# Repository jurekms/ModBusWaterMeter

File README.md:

# ModBusWaterMeter
Nakładka na wodomierz zliczająca impulsy ,udostępniająca dane za pomocą protokołu MODBUS poprzez interfejs RS485.
Nakładka na wodomierz zliczająca ilość obrotów dwubarwnej tarczy znajdującej się na panelu odczytowym wodomierza. Optyczny układ przystawki oświetla tarczę obrotową wodomierza światłem IR, które jest odbijane (część lustrzana tarczy) lub pochłaniane (część czarna tarczy), odbita wiązka jest rejestrowana przez fototranzystor z którego sygnał analogowy kierowany jest do komparatora okienkowego zbudowanego na układzie LM393. Na wyjściu komparatora pojawia się sygnał wysoki - gdy fototranzystor jest oświetlony światłem odbitym od tarczy lub niski gdy światło jest pochłaniane przez tarczę i nie dociera do fototranzystora. Tak uformowany sygnał kierowany jest do wejścia D0 mikroprocesora 368. Oprogramowanie rejestruje dwa impulsy na każdy obrót tarczy - dwa przejścia lustro->czarny i czarny->lustro, co daje dwa impulsy na jeden litr przepływu.

szczegóły w opisie  (https://github.com/jurekms/ModBusWaterMeter/blob/main/WIKI/readme.pdf)

# ModBusWaterMeter
Pulse counting water meter overlay, providing data via the MODBUS protocol via the RS485 interface. Overlay on the water meter counting the number of revolutions of the two-color dial located on the reading panel of the water meter. The optical system of the attachment illuminates the rotating disc of the water meter with IR light, which is reflected (mirror part of the dial) or absorbed (black part of the dial), the reflected beam is recorded by the phototransistor from which the analog signal is directed to a window comparator built on the LM393 system. At the output of the comparator there is a high signal - when the phototransistor is illuminated by light reflected from the dial or low when the light is absorbed by the dial and does not reach the phototransistor. The signal formed in this way is directed to the D0 input of the microprocessor 368. The software records two pulses for each rotation of the dial - two mirror->black and black-> mirror transitions, which gives two pulses per one liter of flow.

more in  (https://github.com/jurekms/ModBusWaterMeter/blob/main/WIKI/readme.pdf)

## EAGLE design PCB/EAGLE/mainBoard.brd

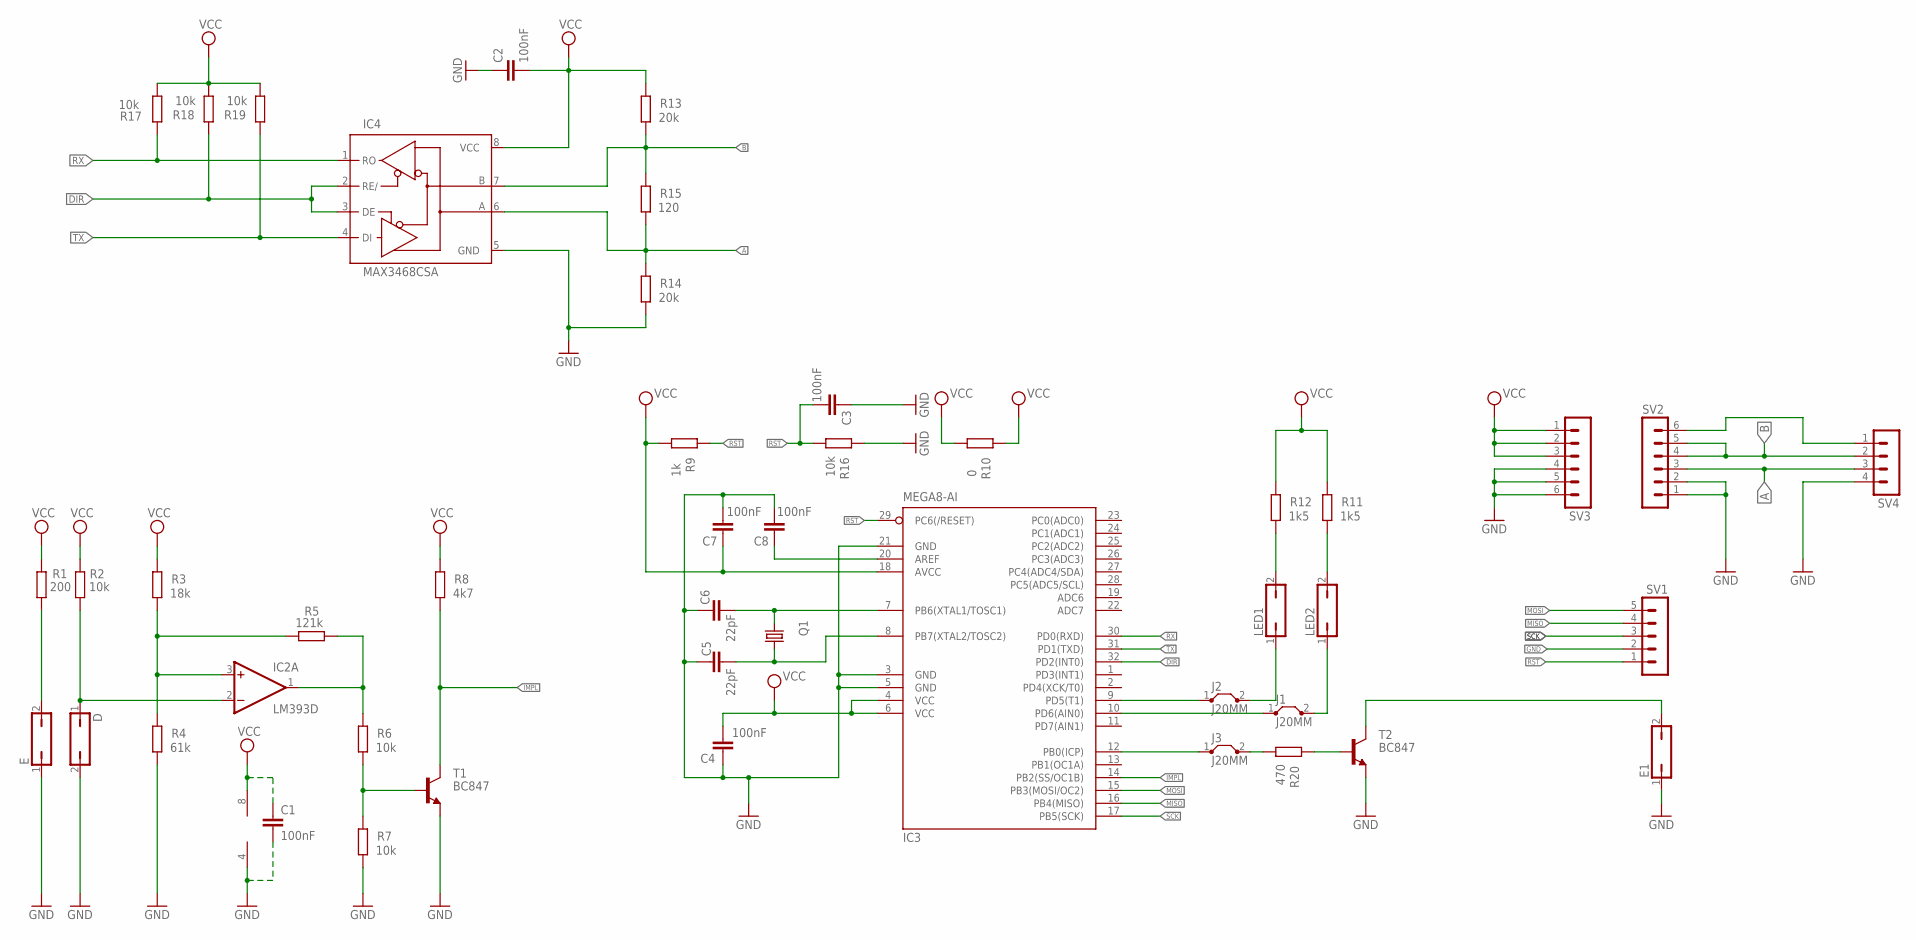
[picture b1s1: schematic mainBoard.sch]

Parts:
C1, C2, C3, C4, C7, C8: 100nF; C1206K
C5, C6: 22pF; C1206K
D: JP1Q; JP1
E, E1: JP1Q; JP1
IC2: LM393D; SO08
IC3: MEGA8-AI; TQFP32-08
IC4: MAX3468CSA; SO08
J1, J2, J3: J20MM; 20
LED1, LED2: JP1Q; JP1
Q1: CRYSTALSM49; SM49
R1: 200; M1206
R2, R6, R7, R16, R17, R18, R19: 10k; M1206
R3: 18k; M1206
R4: 61k; M1206
R5: 121k; M1206
R8: 4k7; M1206
R9: 1k; M1206
R10: 0; M1206
R11, R12: 1k5; M1206
R13, R14: 20k; M1206
R15: 120; M1206
R20: 470; M1206
SV1: MA05-1
SV2, SV3: MA06-1
SV4: MA04-1
T1, T2: BC847; SOT23

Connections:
A: IC4.6 (A), R14.2, R15.1, SV2.3, SV4.3
B: IC4.7 (B), R13.1, R15.2, SV2.4, SV2.5, SV4.2
DIR: IC3.32 (PD2(INT0)), IC4.2 (RE/), IC4.3 (DE), R18.2
GND: C1.2, C2.1, C3.1, C4.1, C5.1, C6.1, C7.2, C8.2, D.2, E.1, E1.1, IC2.4 (V-), IC3.3 (GND), IC3.5 (GND), IC3.21 (GND), IC4.5 (GND), R4.1, R7.1, R14.1, R16.2, SV1.2, SV2.1, SV2.2, SV3.4, SV3.5, SV3.6, SV4.4, T1.2 (E), T2.2 (E)
IMPL: IC3.14 (PB2(SS/OC1B)), R8.1, T1.3 (C)
MISO: IC3.16 (PB4(MISO)), SV1.4
MOSI: IC3.15 (PB3(MOSI/OC2)), SV1.5
unnamed: E.2, R1.1
unnamed: D.1, IC2.2 (-IN), R2.2
unnamed: IC2.3 (+IN), R3.1, R4.2, R5.2
unnamed: R6.1, R7.2, T1.1 (B)
unnamed: IC2.1 (OUT), R5.1, R6.2
unnamed: SV2.6, SV4.1
unnamed: LED2.2, R11.1
unnamed: LED1.2, R12.1
unnamed: C5.2, IC3.8 (PB7(XTAL2/TOSC2)), Q1.1
unnamed: C8.1, IC3.20 (AREF)
unnamed: C6.2, IC3.7 (PB6(XTAL1/TOSC1)), Q1.2
unnamed: J2.2, LED1.1
unnamed: J1.2, LED2.1
unnamed: IC3.9 (PD5(T1)), J2.1
unnamed: IC3.10 (PD6(AIN0)), J1.1
unnamed: IC3.12 (PB0(ICP)), J3.1
unnamed: J3.2, R20.1
unnamed: E1.2, T2.3 (C)
unnamed: R20.2, T2.1 (B)
RST: C3.2, IC3.29 (PC6(/RESET)), R9.2, R16.1, SV1.1
RX: IC3.30 (PD0(RXD)), IC4.1 (RO), R17.1
SCK: IC3.17 (PB5(SCK)), SV1.3
TX: IC3.31 (PD1(TXD)), IC4.4 (DI), R19.2
VCC: C1.1, C2.2, C4.2, C7.1, IC2.8 (V+), IC3.4 (VCC), IC3.6 (VCC), IC3.18 (AVCC), IC4.8 (VCC), R1.2, R2.1, R3.2, R8.2, R9.1, R10.1, R10.2, R11.2, R12.2, R13.2, R17.2, R18.1, R19.1, SV3.1, SV3.2, SV3.3

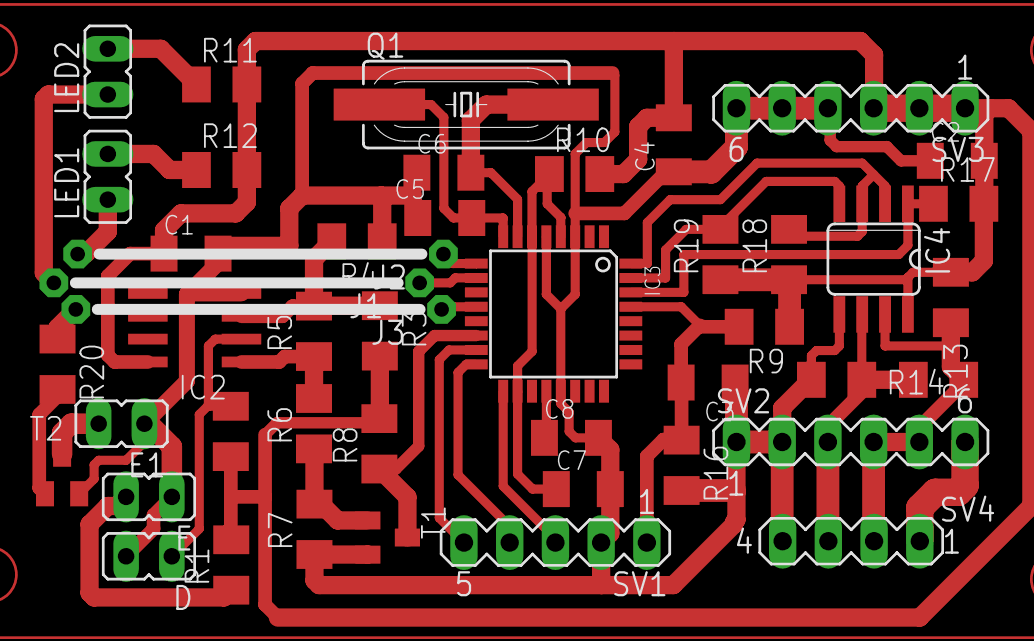
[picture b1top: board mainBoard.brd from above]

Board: 2 copper layers, 46 parts (0 on the bottom side), 31 nets.

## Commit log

2021-12-14 few corrections
2022-02-15 add new description
    add new description
2022-02-15 new version of description
    new version of description
2022-02-25 WIKI changes
    WIKI changes
